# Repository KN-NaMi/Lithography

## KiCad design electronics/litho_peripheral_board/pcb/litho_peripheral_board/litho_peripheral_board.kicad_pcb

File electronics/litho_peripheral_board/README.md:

# litho_peripheral_board

This repository contains the design files and documentation for a custom peripheral control board centered around an **STM32G474 Core Board**. The board is designed to interface with external systems, manage sensors via I2C, and control a 12V pump, while communicating essential data using a **JETSON-formatted protocol** over **UART**.

---

## 🚀 Features

* **Microcontroller:** Utilizes an **STM32G474** (or similar pin-compatible core board) for powerful and efficient control.
* **JETSON Communication:** Dedicated UART interface (`USART_TX`/`USART_RX`) for reliable data exchange, intended for **JETSON-based data packets**.
* **Outside Signal Monitoring:** Input circuit with a **3.3V pull-up** and **LED indicator (D3)** to monitor an external signal (S1).
* **I2C Sensor Interface:** Standard I2C header (J4) for connecting and reading various sensors.
* **Pump Control:** High-side switch **(P-channel MOSFET, Q1)** driven by a PWM signal (`PWM_T_CH1`) for precise **12V pump control** (`pompa_GND`). Includes a flyback diode (D2) for protection.
* **Power Management:**
    * **12V Input:** Fused (`F1`) input for the pump and LDO regulator.
    * **3.3V Regulation:** On-board **LM39100S-3.3 LDO regulator (U1)** converts the 12V supply to a stable **3.3V** for the MCU and logic.

---

## 🧰 Hardware Overview

The board is logically divided into several functional blocks:

### 1. MCU Core
* **MCU:** STM32G474 CoreBoard.
* **Power:** Powered by the regulated **+3.3V** supply.

### 2. JETSON Communication (UART)
* **Connector (J3):** Standard 4-pin header for **UART** connection.
* **Signals:** `USART_TX`, `USART_RX`, `+3.3V`, and `GND`. This is the primary interface for sending/receiving JETSON data.

### 3. Outside Signal
* **Input (S1):** Simple header for connecting an external digital signal.
* **Signal Path:** The input is monitored by a general-purpose I/O pin on the MCU.

### 4. I2C Sensor
* **Connector (J4):** 4-pin header for the I2C bus.
* **Signals:** `SCL_I2C1` and `SDA_I2C1` connect directly to the MCU.

### 5. Pump Control and Power
* **Pump Power (J2):** Fused 12V input with a flyback diode.
* **Pump Control Circuit:** Uses a **PWM signal** from the MCU (`PWM_T_CH1`) to drive a MOSFET (Q1), effectively controlling the power to the pump (`pompa_GND`).
* **LDO Regulator (U1):** Provides the necessary **3.3V** operational voltage.

---

## 🛠️ Usage Notes

### Software
* The **STM32 firmware** must be developed to handle the following:
    * Parsing incoming **JETSON** messages from the `USART_RX` line.
    * Formatting and sending **JETSON** responses on the `USART_TX` line.
    * Reading data from connected **I2C sensors**.
    * Generating the **PWM signal** on the designated pin (e.g., `PB14` or equivalent) to control the pump speed/status.
    * Monitoring the **Outside Signal** input.

### Power
* Ensure the external power supply is **12V DC** and connected correctly to the **J2** header.
* The maximum current draw for the pump should be considered with respect to the fuse (`F1`) rating and the MOSFET (`Q1`) specifications.

---

## 📝 Design Files
The full schematic and PCB layout files are available in the repository.
* **File Name:** `litho_peripheral_board.kicad_sch` (KiCad E.D.A. 5.0.5)

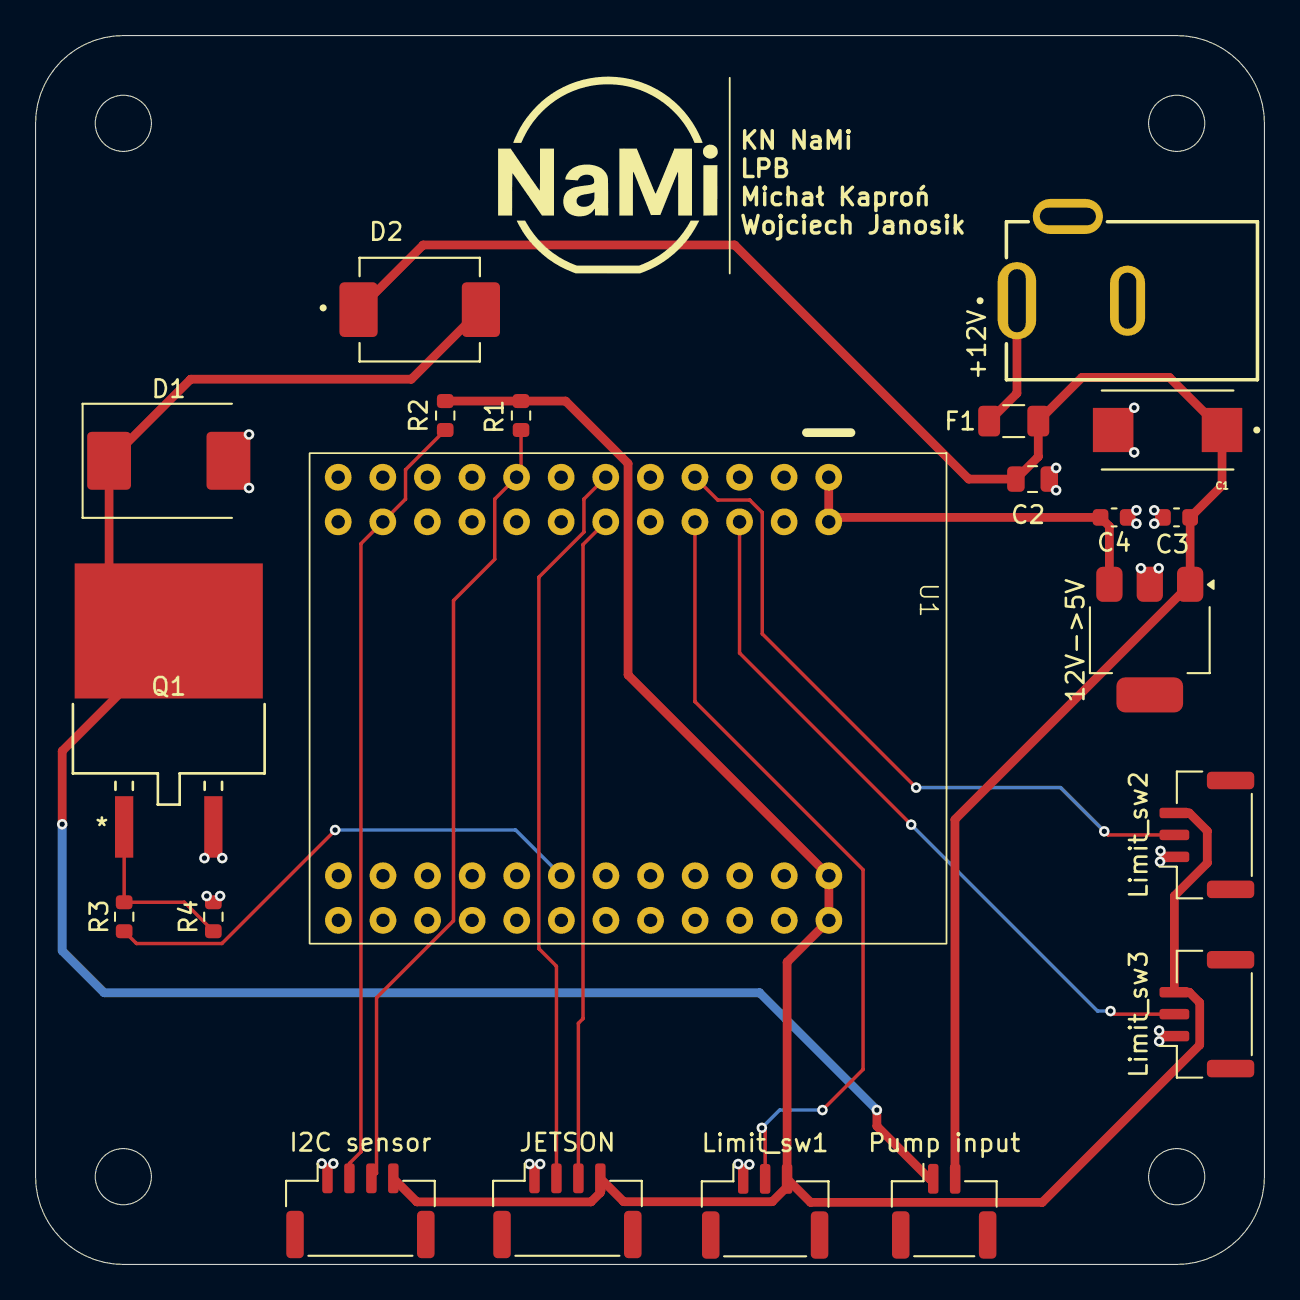
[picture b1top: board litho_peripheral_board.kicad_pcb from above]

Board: 2 copper layers, 70.0 x 70.0 mm, 25 parts (0 on the bottom side), 15 nets.

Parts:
12V->5V: SOT-223
+12V: 12V power supply; GCT_DCJ200-10-A-XX-K_REVA
C1: 100u; CAPPM7343X310N
C2: 10u; C_0805_2012Metric
C3, C4: 100n; C_0603_1608Metric
D1: Schottky_SS32; D_SMC
D2: S3G; DIOM7959X262N
F1: Fuse; Fuse_1206_3216Metric
H1, H2, H3, H4: MountingHole; MountingHole_3.2mm_M3
I2C sensor: I2C output; JST_GH_SM04B-GHS-TB_1x04-1MP_P1.25mm_Horizontal
JETSON: UART_OUTPUT; JST_GH_SM04B-GHS-TB_1x04-1MP_P1.25mm_Horizontal
Limit_sw1, Limit_sw2, Limit_sw3: Conn_01x03_Pin; JST_GH_SM03B-GHS-TB_1x03-1MP_P1.25mm_Horizontal
Pump input: pump; JST_GH_SM02B-GHS-TB_1x02-1MP_P1.25mm_Horizontal
Q1: IRLZ44N; NMOSGDS_D2PAK_INF
R1, R2: 4,7k; R_0603_1608Metric
R3: 100; R_0603_1608Metric
R4: 100k; R_0603_1608Metric
U1: STM32G474CoreBoard

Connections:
+3.3V: I2C sensor.4, JETSON.4, Limit_sw1.3, Limit_sw2.3, Limit_sw3.3, R1.1, R2.1, U1.25 (3V3), U1.26 (3V3)
+5V: 12V->5V.3 (Vout), C4.2, U1.1 (VCC), U1.2 (VCC)
+12V: 12V->5V.1 (Vin), C1.1, C2.1, C3.2, D2.1 (K), F1.2, Pump input.2
GND: 12V->5V.2 (GND), +12V.2, +12V.3, C1.2, C2.2, C3.1, C4.1, D1.2 (A), I2C sensor.1, JETSON.1, Limit_sw1.1, Limit_sw2.1, Limit_sw3.1, Q1.3 (S), R4.2, U1.3 (GND), U1.4 (GND), U1.27 (GND), U1.28 (GND)
unnamed: +12V.1, F1.1
unnamed: Q1.1 (G), R3.2, R4.1
OutSignal1: Limit_sw1.2, U1.8 (PB15)
OutSignal2: Limit_sw2.2, U1.7 (PB14)
OutSignal3: Limit_sw3.2, U1.6 (PB13)
PWM_T2_CH1: R3.1, U1.37 (PA5)
SCL_I2C1: I2C sensor.3, R1.2, U1.15 (PA15)
SDA_I2C1: I2C sensor.2, R2.2, U1.22 (PB7)
UART_RX: JETSON.3, U1.12 (PA10)
UART_TX: JETSON.2, U1.11 (PA9)
pump_minus: D1.1 (K), D2.2 (A), Pump input.1, Q1.2 (D)

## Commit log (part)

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2025-03-18 Init repo
2025-07-02 add frame base
2025-07-03 add corner bracket to frame base
2025-07-03 finish frame
2025-08-27 feat: add scripts
2025-08-28 add gui
2025-08-31 add cube and first lens
2025-09-13 motion
2025-09-22 optics-wip
2025-09-22 wip litho
2025-09-23 first iter of corner plexi mount
2025-09-24 add sidebar and cards
2025-09-27 imporve optidcal system
2025-10-01 init
2025-10-04 feat: add plexi panels and electronics box
2025-10-14 wszystko bez kamery
2025-10-15 wszystko bez kamery v2
2025-10-20 PCB holders
2025-10-22 Partial hinge assembly
    Hinge files and knob added
2025-11-06 Hinge, kob, DIN-bracket, power supply and driver brackets
2025-11-10 Simplified projector model
2025-11-10 Simplified_projector_model
2025-11-16 feat:added LPB to main work tree
2025-11-16 fix: Categorized files according to project standards
2025-11-17 brackets
2025-11-23 Nowy panel i/o
    lepiej zwymiarowany, mniej otworów na śrubki
2025-12-01 Add files via upload
    beta
2025-12-08 Print test 1 (08.12.2025)
2025-12-08 chbgit
2025-12-10 I/O panel V1.0
2025-12-10 Rename cad.zip to cad
2025-12-10 Driver and power supply brackets
2025-12-10 Driver and power supply bracket
2025-12-22 Doorknob
    Doorknob and magnetic catch
2026-01-07 feat: mask upload & view
2026-01-07 feat: mask v2 frfr
2026-01-07 feat: visualization
2026-01-08 Assembly z poprawionym electronic boxem
2026-01-12 fix: clean up using gitignore
2026-01-12 fix: gitignore backups
2026-01-13 Create drilling_template_doorknob.FCStd
    Drilling template
2026-01-28 din mount + din rail
2026-01-28 add codeowners
2026-02-01 fix: asyncio & file validation
2026-02-01 fix: typo
2026-02-01 fix: import
2026-02-01 fix: asyncio condition
2026-02-02 add PS bracket and lrs-150
2026-02-10 feat: first iter of bracket for dlp supply
2026-02-10 feat: refactor api
2026-02-10 feat: add comments to endpoints
2026-02-10 feat: add uv.lock to gitignore
2026-02-11 feat: add dlp power supply bracket
2026-02-12 feat: sketch of bracket
2026-02-13 feat: add bracket to assembly
2026-02-14 update assembly
2026-02-16 add assembly
2026-02-16 fix: masks
2026-02-16 feat: add ruff
2026-02-17 feat: sketch of video streaming
2026-02-17 feat: add image endpoint
2026-02-19 feat: docker & auto update
2026-03-02 Cover do Thorlabs'a
    Zamknięty Part, do zrobienia jeszcze otwarty
2026-03-05 cover v2
2026-03-05 cover v3
2026-03-09 fix: disable reload
2026-03-11 Refactor code structure for improved readability and maintainability
